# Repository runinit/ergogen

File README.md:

# Ergogen

Native configurations use `schema: ergogen/v1`. Read the [living architecture](docs/architecture.md) and [native examples](docs/examples/native/README.md). Historical configs are not accepted by the public API.

***Ergonomic Keyboard Generator***

<br>

The project aims to provide a common configuration format to describe ***ergonomic*** 2D layouts and generate automatic plates, cases, as well as un-routed PCBs for them. The project grew out of (and is an integral part of) the [Absolem keyboard], and shares its [Discord] server as well.

<div align = center>
<br>
<br>
<br>

---

[![Button WebUI]][WebUI]
[![Button Documentation]][Documentation]
[![Button Discord]][Discord]
[![Button Donate]][Donate]

---

</div>

<br>
<br>

## Getting Started

Until there's a proper "Getting started" guide, try getting acquainted with **Ergogen** by following these steps in order:

<br>

1. Read the **[Documentation]**.
    
    D'uuh.
    They're not complete by any measure, but should give you a fairly good idea what you're dealing with here.

    <br>
    
2. Try one of the web-based deployments.

    [![Button Official]][WebUI]   
    [![Button Unofficial]][Unofficial]
   
    (The difference being that Stable runs the latest official release, while Nightly offers early access to in-progress features, both for the Ergogen engine and the UI.)
    
    Load example configs, click things, rewrite things, look at outputs and see if things start to make sense.
   
    There is no need for you to download the **CLI** unless you want to do one of the following:
   
    - Preview in-development features
    - Use custom modifications
    - Contribute code
   
    <br>

3. Search the [`ergogen`][Topic] topic on GitHub.

    There, you can look at (and reverse engineer) a variety of real life configs using **Ergogen**.
    Pop them into the web UI to see what they do, tinker with them and things should start to make more sense.

    <br>

4. If a question persists after all of the above, feel free to ask it over on **[Discord]** and we'll do our best to help you out.

<br>

## Contributions

Feature ideas, documentation improvements, examples, tests, or pull requests welcome!
Get in touch on our **[Discord]**, and we can definitely find something you can help with, if you'd like to.

From an administrative standpoint, please note that we'd like to keep the Git history linear and the test suite comprehensive, so if you do issue a PR, make sure it's A) a straight chain of commits, B) it's always rebased on the current `main`, and C) the test coverage remains at 100%.

<br>

## Sponsors

Huge thanks go to everyone who chooses to support my work!
But even huger thanks are due to the following, *distinguished* sponsors:

- [perce](https://madebyperce.com/)
- [Cache](https://github.com/MvEerd)
- [Neil Gilmour](https://github.com/neilgilmour)
- [ochief](https://github.com/ochief)
- [Alyx Brett](https://github.com/alyx-brett)

<!----------------------------------------------------------------------------->

[Absolem keyboard]: https://zealot.hu/absolem
[Documentation]: https://docs.ergogen.xyz
[Discord]: http://discord.ergogen.xyz
[WebUI]: https://ergogen.xyz
[Unofficial]: https://ergogen.ceoloide.com/
[Topic]: https://github.com/topics/ergogen
[Donate]: https://github.com/sponsors/mrzealot

<!--------------------------------{ Buttons }---------------------------------->

[Button WebUI]: https://img.shields.io/badge/Deployment-37a779?style=for-the-badge&logoColor=white&logo=AppleArcade
[Button Official]: https://img.shields.io/badge/Stable-37a779?style=for-the-badge
[Button Unofficial]: https://img.shields.io/badge/Nightly-yellow?style=for-the-badge
[Button Documentation]: https://img.shields.io/badge/Documentation-1793D1?style=for-the-badge&logoColor=white&logo=GitBook
[Button Discord]: https://img.shields.io/badge/Discord-5865F2?style=for-the-badge&logoColor=white&logo=Discord
[Button Donate]: https://img.shields.io/badge/Donate-EA4AAA?style=for-the-badge&logoColor=white&logo=githubsponsors

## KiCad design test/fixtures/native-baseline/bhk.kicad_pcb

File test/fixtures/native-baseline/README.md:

# BHK baseline

Captured before the native API change: original YAML, canonical configuration,
51 resolved placement points, and KiCad output. `providers.json` contains the 13
pinned footprint modules used by that source, for reproducible offline tests.

Native acceptance compares all original XY/rotation values and all 145 emitted
footprints / 1,122 pads (including net names). KiCad 10's equivalent stroke
syntax is normalized for comparison. Board perimeter geometry intentionally
changes to the explicit native cluster boundary. These fixtures establish
software parity, not electrical or fabrication approval.

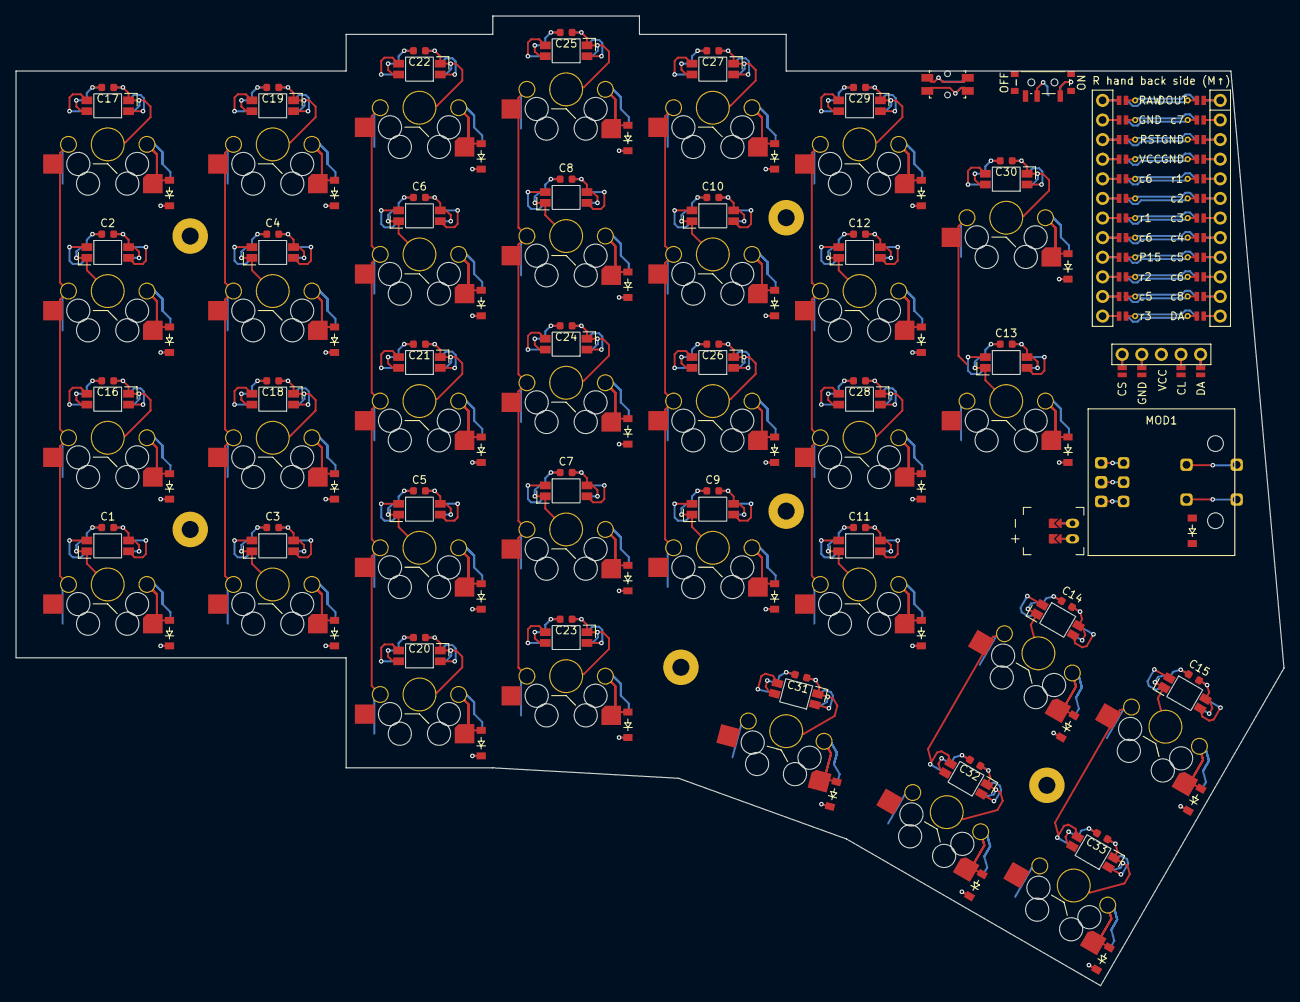
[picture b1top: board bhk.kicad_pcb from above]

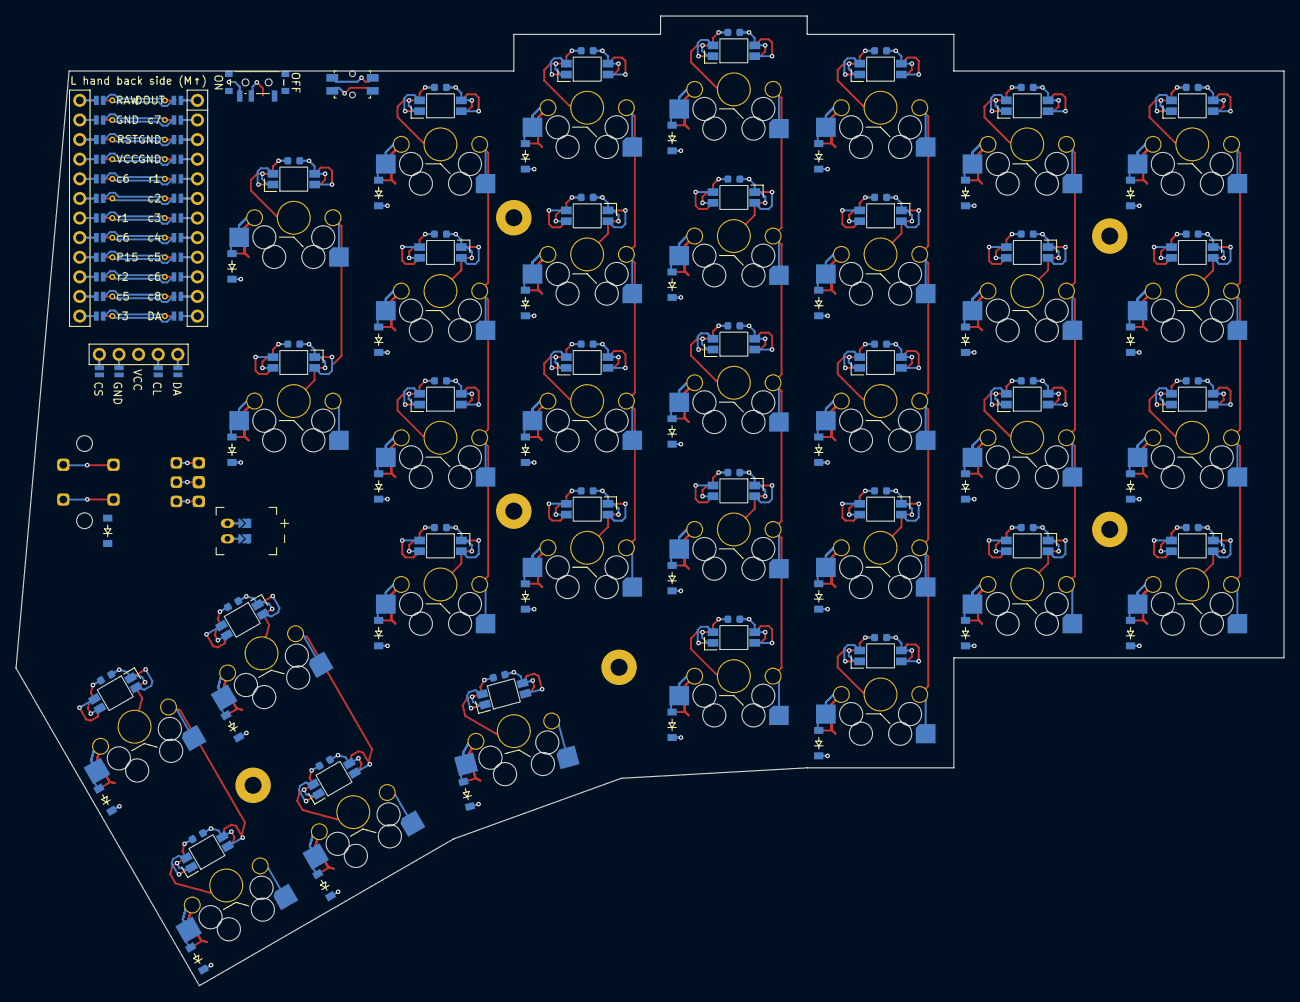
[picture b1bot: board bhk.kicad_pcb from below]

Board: 2 copper layers, 164.2 x 125.6 mm, 145 parts (67 on the bottom side), 93 nets.

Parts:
C1, C2, C3, C4, C5, C6, C7, C8, C9, C10, C11, C12, C13, C14, C15, C16, C17, C18, C19, C20, C21, C22, C23, C24, C25, C26, C27, C28, C29, C30, C31, C32, C33: Capacitor_0603
D1, D2, D3, D4, D5, D6, D7, D8, D9, D10, D11, D12, D13, D14, D15, D16, D17, D18, D19, D20, D21, D22, D23, D24, D25, D26, D27, D28, D29, D30, D31, D32, D33, D34: diode_tht_sod123
DISP1: display_nice_view
H1, H2, H3, H4, H5, H6: mounting_hole_plated
JST1: battery_connector_jst_ph_2
LED1, LED2, LED3, LED4, LED5, LED6, LED7, LED8, LED9, LED10, LED11, LED12, LED13, LED14, LED15, LED16, LED17, LED18, LED19, LED20, LED21, LED22, LED23, LED24, LED25, LED26, LED27, LED28, LED29, LED30, LED31, LED32, LED33: led_SK6812mini-e (per-key, reversible)
MCU1: mcu_supermini_nrf52840
MOD1: THQWGD001C
PWR1: power_switch_smd_side
RST1: reset_switch_smd_side
S1, S2, S3, S4, S5, S6, S7, S8, S9, S10, S11, S12, S13, S14, S15, S16, S17, S18, S19, S20, S21, S22, S23, S24, S25, S26, S27, S28, S29, S30, S31, S32, S33: switch_mx

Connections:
BAT_P: JST1.1, PWR1.1, PWR1.3
CL: DISP1.12, DISP1.22
CS: DISP1.10, DISP1.20
DA: DISP1.13, DISP1.23, MCU1.112
DISP1_1: DISP1.1, DISP1.14, DISP1.27
DISP1_2: DISP1.2, DISP1.15, DISP1.26
DISP1_4: DISP1.4, DISP1.16, DISP1.25
DISP1_5: DISP1.5, DISP1.17, DISP1.24
DOUT: LED30.4, MCU1.101
GND: C1.1, C2.1, C3.1, C4.1, C5.1, C6.1, C7.1, C8.1, C9.1, C10.1, C11.1, C12.1, C13.1, C14.1, C15.1, C16.1, C17.1, C18.1, C19.1, C20.1, C21.1, C22.1, C23.1, C24.1, C25.1, C26.1, C27.1, C28.1, C29.1, C30.1, C31.1, C32.1, C33.1, DISP1.11, DISP1.21, JST1.2, LED1.3, LED2.3, LED3.3, LED4.3, LED5.3, LED6.3, LED7.3, LED8.3, LED9.3, LED10.3, LED11.3, LED12.3, LED13.3, LED14.3, LED15.3, LED16.3, LED17.3, LED18.3, LED19.3, LED20.3, LED21.3, LED22.3, LED23.3, LED24.3, LED25.3, LED26.3, LED27.3, LED28.3, LED29.3, LED30.3, LED31.3, LED32.3, LED33.3, MCU1.103, MCU1.104, MCU1.123, MOD1.1, MOD1.2, MOD1.C, RST1.1, RST1.3
JST1_1: JST1.11, JST1.21, JST1.31
JST1_2: JST1.12, JST1.22, JST1.32
LED_1: LED29.4, LED30.2
LED_2: LED27.4, LED29.2
LED_3: LED25.4, LED27.2
LED_4: LED22.4, LED25.2
LED_5: LED19.4, LED22.2
LED_6: LED17.4, LED19.2
LED_7: LED2.4, LED17.2
LED_8: LED2.2, LED4.4
LED_9: LED4.2, LED6.4
LED_10: LED6.2, LED8.4
LED_11: LED8.2, LED10.4
LED_12: LED10.2, LED12.4
LED_13: LED12.2, LED13.4
LED_14: LED13.2, LED28.4
LED_15: LED26.4, LED28.2
LED_16: LED24.4, LED26.2
LED_17: LED21.4, LED24.2
LED_18: LED18.4, LED21.2
LED_19: LED16.4, LED18.2
LED_20: LED1.4, LED16.2
LED_21: LED1.2, LED3.4
LED_22: LED3.2, LED5.4
LED_23: LED5.2, LED7.4
LED_24: LED7.2, LED9.4
LED_25: LED9.2, LED11.4
LED_26: LED11.2, LED14.4
LED_27: LED14.2, LED15.4
LED_28: LED15.2, LED33.4
LED_29: LED32.4, LED33.2
LED_30: LED31.4, LED32.2
LED_31: LED23.4, LED31.2
LED_32: LED20.4, LED23.2
RAW: MCU1.124, PWR1.2
RST: MCU1.122, RST1.2, RST1.4
VCC: C1.2, C2.2, C3.2, C4.2, C5.2, C6.2, C7.2, C8.2, C9.2, C10.2, C11.2, C12.2, C13.2, C14.2, C15.2, C16.2, C17.2, C18.2, C19.2, C20.2, C21.2, C22.2, C23.2, C24.2, C25.2, C26.2, C27.2, C28.2, C29.2, C30.2, C31.2, C32.2, C33.2, DISP1.3, LED1.1, LED2.1, LED3.1, LED4.1, LED5.1, LED6.1, LED7.1, LED8.1, LED9.1, LED10.1, LED11.1, LED12.1, LED13.1, LED14.1, LED15.1, LED16.1, LED17.1, LED18.1, LED19.1, LED20.1, LED21.1, LED22.1, LED23.1, LED24.1, LED25.1, LED26.1, LED27.1, LED28.1, LED29.1, LED30.1, LED31.1, LED32.1, LED33.1, MCU1.121
c1: S1.1, S1.2, S2.1, S2.2, S3.1, S3.2, S4.1, S4.2
c1_r1: D4.2, S4.1, S4.2
c1_r2: D3.2, S3.1, S3.2
c1_r3: D2.2, S2.1, S2.2
c1_r4: D1.2, S1.1, S1.2
c2: MCU1.106, S5.1, S5.2, S6.1, S6.2, S7.1, S7.2, S8.1, S8.2
c2_r1: D8.2, S8.1, S8.2
c2_r2: D7.2, S7.1, S7.2
c2_r3: D6.2, S6.1, S6.2
c2_r4: D5.2, S5.1, S5.2
c3: MCU1.107, S9.1, S9.2, S10.1, S10.2, S11.1, S11.2, S12.1, S12.2, S13.1, S13.2
c3_r1: D13.2, S13.1, S13.2
c3_r2: D12.2, S12.1, S12.2
c3_r3: D11.2, S11.1, S11.2
c3_r4: D10.2, S10.1, S10.2
c3_r5: D9.2, S9.1, S9.2
c4: MCU1.108, S14.1, S14.2, S15.1, S15.2, S16.1, S16.2, S17.1, S17.2, S18.1, S18.2
c4_r1: D18.2, S18.1, S18.2
c4_r2: D17.2, S17.1, S17.2
c4_r3: D16.2, S16.1, S16.2
c4_r4: D15.2, S15.1, S15.2
c4_r5: D14.2, S14.1, S14.2
c5: MCU1.109, MCU1.114, S19.1, S19.2, S20.1, S20.2, S21.1, S21.2, S22.1, S22.2, S29.1, S29.2
c5_r1: D22.2, S22.1, S22.2
c5_r2: D21.2, S21.1, S21.2
c5_r3: D20.2, S20.1, S20.2
c5_r4: D19.2, S19.1, S19.2
c5_r5: D29.2, S29.1, S29.2
c6: MCU1.110, MCU1.117, MCU1.120, S23.1, S23.2, S24.1, S24.2, S25.1, S25.2, S26.1, S26.2, S31.1, S31.2
c6_r1: D26.2, S26.1, S26.2
c6_r2: D25.2, S25.1, S25.2
c6_r3: D24.2, S24.1, S24.2
c6_r4: D23.2, S23.1, S23.2
c6_r5: D31.2, S31.1, S31.2
c7: MCU1.102, S27.1, S27.2, S28.1, S28.2, S30.1, S30.2
c7_r1: D28.2, S28.1, S28.2
c7_r2: D27.2, S27.1, S27.2
c7_r4: D30.2, S30.1, S30.2
c8: MCU1.111, S32.1, S32.2, S33.1, S33.2
c8_r4: D32.2, S32.1, S32.2
c8_r5: D33.2, S33.1, S33.2
r1: D4.1, D8.1, D13.1, D18.1, D22.1, D26.1, D28.1, MCU1.105, MCU1.118
r2: D3.1, D7.1, D12.1, D17.1, D21.1, D25.1, D27.1, MCU1.115
r3: D2.1, D6.1, D11.1, D16.1, D20.1, D24.1, D34.1, MCU1.113
r4: D1.1, D5.1, D10.1, D15.1, D19.1, D23.1, D30.1, D32.1
r5: D9.1, D14.1, D29.1, D31.1, D33.1
